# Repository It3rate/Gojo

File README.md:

# Gojo

Gojo is a lean extraction of the current Gojo kernel and tests from the older Core4 workspace.

The central rule is that meaning should live in inspectable Gojo structure: carriers, locations, relations, unit shapes, slots, residue, timelines, and tension. Helper code may build or read that structure, but it should not become the source of meaning.

For reusable encoding code, start with the [shared encoding core](Gojo.Encoding/Core/README.md):
packed storage and ports, native laws and machines, and connected construction
reads promoted from the experiments. New studies can reuse these mechanisms
while keeping unfinished additions local.

For the research, start with the [experiment overview](experiments/OVERVIEW.md):
a chronological guide to the studies in `experiments/`, with each study's
question, results, conclusions and links to the evidence.

The [evidence calculation fixture](Gojo/docs/GojoEvidenceCalculationFixture.md)
tests finite Bayesian conditioning, question orientation, evidence dependence
and empirical support using native unmeasured partitions. Its
[gallery](experiments/QualitativeFrieze/results/evidence-calculation/gallery.html)
uses square continuations to check calculation laws, with supplied likelihoods.

The [weighted shape experiment](Gojo/docs/GojoWeightedShapeEvidence.md) applies
those laws to the 100-shape corpus, comparing the same frozen receiver
proposals under estimated likelihoods and revisable priors. Its
[gallery](experiments/QualitativeFrieze/results/weighted-shapes/gallery.html)
keeps source audits separate from conditional selection weights.

The [mixed curve study](Gojo/docs/GojoQualitativeCurveEvidence.md) adds native
straight, quadratic and cubic constructions, tangent/corner/cusp reads, and
explicit interior and gap-completion premises. Its
[gallery](experiments/QualitativeFrieze/results/curve-evidence/gallery.html)
compares 24 sources and 72 receiver constructions on supplied anonymous endpoint
scaffolds, including a weak whole-shape diamond read alongside local notches.

The [compound ornament study](Gojo/docs/GojoOrnamentCompositionStudy.md) composes
curved bands into shared motifs, mirrored placements, feedback orbits and
two-dimensional fields. Its [16-design gallery](experiments/QualitativeFrieze/results/ornament-composition/gallery.html)
retains frames, repeat correspondence and separately assessed colour intentions.

The [substrate ornament study](Gojo/docs/GojoOrnamentSubstrateStudy.md) keeps
continuous strands independent of their repeat events. Its
[12-design gallery](experiments/QualitativeFrieze/results/ornament-substrate/gallery.html)
includes weave, twill, wave/ogee courses and curved interlocking cells, with
shared local profiles and complete opposite-boundary correspondence.

The [integrated motif pass](Gojo/docs/GojoOrnamentIntegratedStudy.md) adds larger
rooted leaves and landmark florets while preserving those exact mesh paths.
Its [before/after gallery](experiments/QualitativeFrieze/results/ornament-integrated/gallery.html)
exposes native endpoint and straight-interior attachments, tangent reads and
the carried earlier decoration.

The [interior ornament pass](Gojo/docs/GojoOrnamentInteriorStudy.md) develops
multi-part flowers, fans and scrolls within mesh compartments, with native
interior construction landmarks and reusable guide-derived petal profiles.
See the [before/after inspector](experiments/QualitativeFrieze/results/ornament-interior/gallery.html)
and [all new designs](experiments/QualitativeFrieze/results/ornament-interior/designs.html).

The [path and band study](Gojo/docs/GojoPathBandStudy.md) connects source paths,
paired sides, selected occupancy, caps/continuation and local crossing order.
Its [22-case gallery](experiments/QualitativeFrieze/results/path-bands/gallery.html)
shows narrow and broad constructions while retaining the same native paths.

The [curve refinement study](Gojo/docs/GojoCurveRefinementStudy.md) adds relative
fullness, directional and tangent-curvature balance, provisional interiors and
centre/enclosure contexts. Its
[112-case gallery](experiments/QualitativeFrieze/results/curve-refinement/gallery.html)
compares native cue bands, local receiver fitting and revisable completion
defaults while retaining contrary evidence and unresolved interpretations.

The [relational shape study](Gojo/docs/GojoRelationalShapeStudy.md) reconstructs
100 sources with separate pairwise spatial cues, length and angle equivalence,
and qualitative support and opposition. Its
[gallery](experiments/QualitativeFrieze/results/relational-shapes/gallery.html)
compares observation, requested completion, sparse evidence and a control
withholding equivalence. Layout and closure remain revisable hypotheses.

The [joint composition study](Gojo/docs/GojoJointCompositionReconstruction.md)
reconstructs native shapes from anonymous joints, ordinal positions and separate
symmetry evidence. Its [gallery](experiments/QualitativeFrieze/results/joint-reconstruction/gallery.html)
compares three authored policies, retained assumptions and message-only feedback;
this composition round does not train a model.

The [ornament learning pilot](Gojo/docs/GojoOrnamentLearningPilot.md) trains a
portable native route dictionary from a streamed curriculum and tests partial
evidence, conflicts and held-out constructions. Its
[gallery](experiments/QualitativeFrieze/results/ornament-learning/gallery.html)
keeps teacher observations, open correspondence and generated hypotheses
separate; [whole-family holdout](experiments/QualitativeFrieze/results/ornament-learning-family/gallery.html)
exposes the limits of route recall without compositional learning.

The [native interior discovery study](Gojo/docs/GojoNativeInteriorDiscovery.md)
finds local enclosures in lattice passages through native word order and cyclic
ray walks, then reads side structure, notches and zigzags with explicit evidence.
Its [gallery](experiments/QualitativeFrieze/results/native-interiors/gallery.html)
separates observed boundaries from proposed gap closures; the
[overview](experiments/QualitativeFrieze/results/native-interiors/overview.html)
compares twenty source patches.

The [native lattice evidence study](Gojo/docs/GojoNativeLatticeEvidence.md)
connects executed ornament graphs to query-directed geometric evidence through
published ports. Its [gallery](experiments/QualitativeFrieze/results/native-lattice-evidence/gallery.html)
compares actual source supports, requested premises and derived boundary views,
including missing geometry and bounded searches.

The [structural potential study](Gojo/docs/GojoStructuralPotential.md) connects
partial evidence to query-directed relational completions. Its
[gallery](experiments/QualitativeFrieze/results/structural-potential/gallery.html)
keeps supporting-line possibilities, finite support, and introduced assumptions
separate from the original source.

The [reusable rule-pack study](Gojo/docs/GojoReusableRulePacks.md) applies the same
native contracts to ornaments, glyphs and path networks, then connects defaults
to provisional generation and revision. Its
[interactive gallery](experiments/QualitativeFrieze/results/rule-pack-transfer/gallery.html)
keeps source evidence, construction assumptions and actual output checks separate.

The [ornament default study](Gojo/docs/GojoOrnamentDefaults.md) separates required
structure, revisable defaults and deliberately unused cues across 72 native
drawings. Its [interactive gallery](experiments/QualitativeFrieze/results/ornament-defaults/gallery.html)
shows which alternatives survive changes to count, symmetry, overlap and
proportion expectations, with counterexamples and missing evidence retained.

The [ornament concept-equivalence study](Gojo/docs/GojoOrnamentConceptEquivalence.md)
compares 38 native designs under explicit whole-arrangement questions. Its
[interactive gallery](experiments/QualitativeFrieze/results/ornament-concepts/gallery.html)
shows how a rosette, fan and branching window can share one route concept while
remaining visually different, and exposes designs that agree with earlier local
questions but violate the requested whole arrangement.

## Quick Start

Work directly on `master` and commit completed, verified checkpoints locally.
Create a feature branch only when requested. Pushing remains a separate action.

```powershell
dotnet test Gojo.slnx
```

## Layout

The [Minds notebook](experiments/Minds/README.md) retains the two-space feedback and
prospective prediction experiments, including protocols, recorded outcomes,
independent comparisons and the static `/minds/` viewers.

```text
Gojo/                       numeric and structural kernel
  Core/                     carriers, locations, relations, tick refs, unit shapes
  Structures/               repeat surfaces, claims and other structural helpers
  Patterns/                 placeholders, bindings and repeat controllers
  Equations/                relation-shaped equations and reads
  ConceptSurface/           low-resolution concept-surface experiments
  axioms/                   current model notes
  docs/                     model documentation and experiment reports
Gojo.Encoding/              experimental encoding and concept-address layer
Gojo.EncodingC/             lean bit-level encoding of computing structures (exploratory)
Applications/
  GojoCAD/                  graphical and geometric Gojo structure
  GojoDraw/                 Skia presentation adapter over GojoCAD
Visualizations/
  Gojo.Blocks/               interactive structural explorer
  Gojo.Blocks.Browser/       browser host for Blocks
  Gojo.GearShapeLadder/      gear and shape-ladder explorer
  Gojo.GearShapeLadder.Browser/
  GojoCAD.SketchViewer/      sketch inspection UI
  GojoCAD.SketchViewer.Browser/
  GojoDraw.Visualizer/       demo app exercising GojoDraw
  Gojo.Demos.Web/            static experiment viewers
Tests/                      every test project, retaining its existing name
experiments/                research fixtures, runners and retained results
  Minds/                    two-space feedback and prediction notebook
artifacts/                  generated build and export artifacts
```

Solution folders follow these same categories. Each solution keeps its existing
project selection; some retained experiments and viewers are run directly.
Project names, assemblies and namespaces remain unchanged by this layout.

## Extracted From

This repo was extracted from the Core4 workspace so Gojo can be read and developed without the older Core4, runtime, demo, SIMD, and probe projects in the way.

Older ideas worth remembering are summarized in the
[Core4 idea inventory](Gojo/docs/LegacyCore4IdeaInventory.md); they should be
re-expressed Gojo-natively before becoming code.

## Simulation and learning experiments

The experiments are retained on `master`, including the Minds notebook,
Phototaxis swimming demo, prediction and market studies, and later learning,
composition and lifecycle work. Read the [chronological overview](experiments/OVERVIEW.md)
for findings, or the [experiment index](experiments/README.md) for runnable
commands, retained results and the lossless large-result restore helper.

The [qualitative recognition study](Gojo/docs/GojoQualitativeRecognition.md)
examines recurring motifs and larger flow arrangements from segment observations
with construction history and position words withheld. Its retained
[interactive gallery](experiments/QualitativeFrieze/results/qualitative-recognition/gallery.html)
compares several interpretations of each field.
The [evidence and placement follow-up](Gojo/docs/GojoQualitativeRecognitionFirmness.md)
separates admission from demonstrated flow, adds ordinal chamber placement,
and rechecks preserved motifs against local changes in its
[gallery](experiments/QualitativeFrieze/results/recognition-firmness/gallery.html).
The [hierarchical recognition study](Gojo/docs/GojoHierarchicalRecognition.md)
composes motifs, chamber roles and row programs across opaque interfaces.
Its [interactive gallery](experiments/QualitativeFrieze/results/hierarchical-recognition/gallery.html)
follows questions downward and actual evidence back upward, including contrary,
ambiguous and capacity-limited answers.
The [ornament program encoding](Gojo/docs/GojoOrnamentProgramEncoding.md)
separates shared motifs and periodic layout rules from parameter bindings,
sampling windows and expanded execution. Its
[gallery](experiments/QualitativeFrieze/results/ornament-program/gallery.html)
includes six samples from a saved native program, with standalone replay.
The [Bourgoin construction study](Gojo/docs/GojoBourgoinEncodingStudy.md)
tests a broader source-derived vocabulary and explicit seams between repeated
units. Its [comparison gallery](experiments/QualitativeFrieze/results/bourgoin-patterns/gallery.html)
places native generated fields beside the cited historical diagrams.
The [source-correction follow-up](Gojo/docs/GojoBourgoinRefinementStudy.md)
uses local lattice refinements and closed negative chambers to improve those
reconstructions, with preserved first-pass images and source overlays.
The [construction vocabulary study](Gojo/docs/GojoBourgoinVocabularyStudy.md)
adds twenty source-based skeletons, finite curved profiles and a
[single-sheet atlas](experiments/QualitativeFrieze/results/bourgoin-patterns/overview.html),
while separating authored explanations from computed graph reads.
The [contact and course study](Gojo/docs/GojoBourgoinContactAndCourseStudy.md)
refines partial-side sliding contacts, flat-tipped stars, slender arms and
open ribbon courses while retaining the earlier constructions for comparison.
The [lattice construction ladders](Gojo/docs/GojoLatticeConstructionLadders.md)
retain actual grid ancestors through 19 related constructions, with separate
current-graph questions and an explicit history-forgetting experiment. Their
[interactive gallery](experiments/QualitativeFrieze/results/lattice-ladders/gallery.html)
lets you walk each branch and compare its earlier bases.
The [hundred-lattice catalogue](Gojo/docs/GojoLatticeCatalogue.md) expands this
into twenty parameterized families with explicit constraint withdrawal,
reformulation, coarse compartments and finite rule assessments. Its
[gallery](experiments/QualitativeFrieze/results/lattice-catalogue/gallery.html)
shows construction strips and supports local ratings; the
[whole sheet](experiments/QualitativeFrieze/results/lattice-catalogue/overview.html)
compares all hundred unfilled scaffolds.
The [geometric transformation follow-up](Gojo/docs/GojoLatticeGeometryTransformations.md)
then changes the actual spans with notches, bends, cuts, shared runs and moved
hubs. Its [before/after gallery](experiments/QualitativeFrieze/results/lattice-transformations/gallery.html)
separates real support change from regrouping or rescaling the same pattern.
The [interior-first study](Gojo/docs/GojoLatticeInteriorStudy.md) merges actual
atomic faces into non-overlapping cells, with explicit competing seam claims.
Its [hundred-case gallery](experiments/QualitativeFrieze/results/lattice-interiors/gallery.html)
compares filled interiors, outlines and removed dividers.
The [Gestalt exploration plan](Gojo/docs/GojoGestaltViewsExploration.md) proposes
overlapping cue-based reads and compares constructive contexts for the same shape.
The [construction-context experiments](Gojo/docs/GojoConstructionContextExperiments.md)
exercise equal support with different edit scopes, constraint withdrawal,
optional construction memory and overlapping views consumed by new flow.
Their [interactive gallery](experiments/QualitativeFrieze/results/construction-contexts/gallery.html)
and [all-step overview](experiments/QualitativeFrieze/results/construction-contexts/overview.html)
compare seventeen path steps and three shared-field constructions.
The [junction interpretation study](Gojo/docs/GojoJunctionInterpretationExperiments.md)
then separates actual joins from projected crossings, endpoint contacts and
speculative gap continuations. Its [gallery](experiments/QualitativeFrieze/results/junction-interpretations/gallery.html)
retains competing cut and depth readings without altering source topology.
The [coloured ornament collection](experiments/QualitativeFrieze/results/coloured-ornament/gallery.html)
adds native landmark-bound petals, leaves and medallions, with three selectable
focuses guided by Jones's colour and hierarchy proposals. Its
[study](Gojo/docs/GojoColouredOrnamentStudy.md) also corrects B32's diagonal continuation.
The [full ornament design collection](experiments/QualitativeFrieze/results/ornament-designs/gallery.html)
extends all 36 skeletons into 108 separately constructed designs, with
geometric fields, intermediate flowers and foliage, and fine local details.
Its [single-page sheet](experiments/QualitativeFrieze/results/ornament-designs/overview.html)
puts all three versions of every skeleton together; the
[construction study](Gojo/docs/GojoOrnamentDesignCollection.md) describes the
finer unmeasured vocabulary and native attachment evidence.
The [detail study](experiments/QualitativeFrieze/results/ornament-details/gallery.html)
develops ten richer motifs and four scaffold-following B02/B05 integrations,
with one-unit close-ups and a single comparison sheet.
The [refined 108-design collection](experiments/QualitativeFrieze/results/ornament-refined/gallery.html)
extends that vocabulary across the catalogue with optional curves over native
guides, angular comparisons and close-ups. The
[curve studies](experiments/QualitativeFrieze/results/ornament-curves/gallery.html)
isolate the vine, corrected curl and interrupted guilloche.
The [B08–B14 interior studies](experiments/QualitativeFrieze/results/ornament-refined/interiors-gallery.html)
develop larger flowers, interior gardens and four-colour interlocking shapes,
with [24 designs on one sheet](experiments/QualitativeFrieze/results/ornament-refined/interiors.html).
The [silhouette and colour review](experiments/QualitativeFrieze/results/ornament-refined/balance.html)
compares the enlarged detail with its previous checkpoint; a
[conceptual-complexity table](experiments/QualitativeFrieze/results/ornament-refined/complexity.html)
keeps reviewed reusable vocabularies separate from native encoding counts.
The [public ornament gallery](https://gojo.inklingai.ca/ornaments/flowing-grammar/)
includes all 108 designs and their executed-unit views. Its bounded website
edition keeps the research archives and alternate construction views in this checkout.

For example, run the prospective-prediction experiment and its notebook tests
from the repository root:

```powershell
dotnet run --project experiments/Minds -- --experiment3
dotnet test Tests/Minds.Tests/Minds.Tests.csproj
```

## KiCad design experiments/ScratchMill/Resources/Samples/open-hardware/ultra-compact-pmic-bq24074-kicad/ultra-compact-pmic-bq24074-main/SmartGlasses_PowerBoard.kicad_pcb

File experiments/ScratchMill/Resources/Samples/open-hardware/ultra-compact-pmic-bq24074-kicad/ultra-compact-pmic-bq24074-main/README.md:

# ultra-compact-pmic-bq24074

## 1. Project Overview
This repository contains the design files for an ultra-compact (11mm x 30mm) Power Management Unit (PMU) specifically engineered for wearable AR/VR devices. The module is built around the **Texas Instruments BQ24074** PMIC, providing a unified solution for USB Type-C power input, Lithium-Polymer battery charging, and regulated system output (VOUT).

The design prioritizes high power density, stringent thermal management, and IPC-compliant routing within a highly constrained physical footprint.

## 2. Technical Specifications
* **Form Factor:** 11mm x 30mm (Edge-mount optimized)
* **PMIC:** TI BQ24074 (Standalone Li-Ion/Li-Pol Charger with Power Path Management)
* **Input (VBUS):** USB Type-C Receptacle (6-Pin, Power Only, Edge-Mount)
* **Output Interface:** 5-Pin 0.5mm Pitch Horizontal FPC Connector
* **Protection:** ESD and Transient Voltage Suppression (TVS) on VBUS (DFN1006 package)
* **Component Sizing:** Optimized for 0201 (Imperial) passive components to minimize parasitic inductance and footprint.

## 3. Engineering Analysis & Design Methodology

### 3.1 Layout and I/O Integration
* **Mechanical Alignment:** The J1 Type-C connector is positioned with mechanical GND pads flush to the board edge (Edge.Cuts), ensuring structural integrity and precise alignment for wearable frames.
* **Isolation Zones:** Battery termination pads (BATT+/BATT-) are isolated from the main PMIC logic to prevent short circuits during manual soldering/assembly.

### 3.2 Power Integrity and Thermal Strategy
* **High-Current Pathing:** VBUS, VOUT, and BAT tracks are routed with a minimum width of 0.5mm to sustain peak charging currents and minimize IR drop.
* **Decoupling Protocol:** Low-ESR ceramic capacitors (C1, C2) are placed in immediate proximity to the PMIC pins to suppress high-frequency noise and ensure voltage stability.
* **Ground Plane & Via Stitching:** A dual-layer solid ground plane strategy was employed. Isolated GND islands on the top layer are interconnected to the primary bottom layer ground plane through a high-density via stitching matrix. This facilitates both low-impedance return paths and efficient thermal dissipation for the BQ24074.

### 3.3 Verification
* **DRC Compliance:** 0 Design Rule Check (DRC) violations based on 0.1mm minimum clearance constraints.
* **Manufacturing Ready:** All footprints and clearances are verified for standard SMT assembly processes.

## 4. Repository Structure

The production files are organized according to industry-standard fabrication requirements:

1. **`1_Gerber_Files/`** : Fabrication data (.gbr) and drill files (.drl) for PCB manufacturing.
2. **`2_Pick_And_Place/`** : Component centroid data (.pos / .csv) for automated SMT assembly.
3. **`3_BOM_List/`** : Consolidated Bill of Materials including manufacturer part numbers and footprints.
4. **`4_Documentation/`** : High-resolution schematic (PDF) and design specifications.

## 5. Mechanical Integration Note
The current revision (Rev 1.0) focuses on electrical validation and thermal optimization. 3D STEP models for mechanical components (USB-C, FPC, and Tactile Switch) are excluded from this release to allow for custom mechanical alignment with specific frame geometries.

## 6. License
This project is licensed under the **CERN Open Hardware Licence Version 2 - Permissive (CERN-OHL-P)**. See the `LICENSE` file for more details.
---
*Designer:* **Mustafa Ege KILIÇ** *Date:*  08 April 2026  
*Project Version:* Rev 1.0

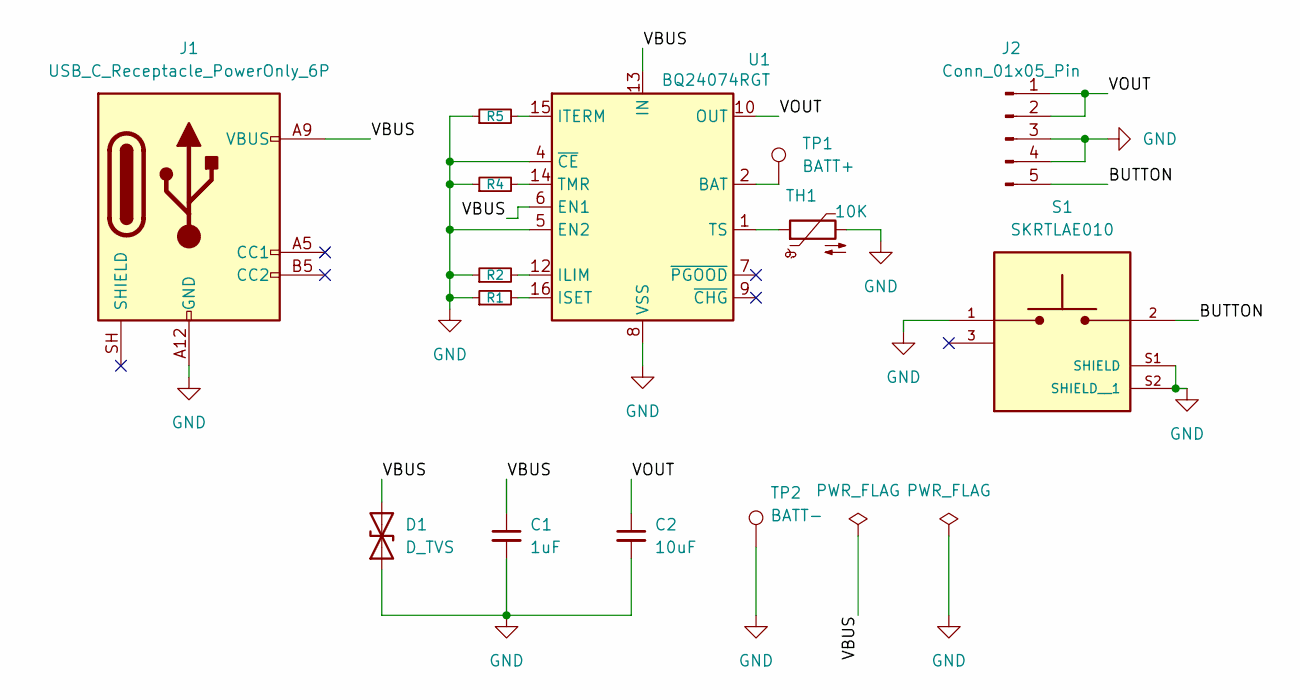
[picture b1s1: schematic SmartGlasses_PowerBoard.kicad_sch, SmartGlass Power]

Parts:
C1: 1uF; C_0402_1005Metric
C2: 10uF; C_0603_1608Metric
D1: D_TVS; D_0402_1005Metric
J1: USB_C_Receptacle_PowerOnly_6P; CONN_USB4135-GF-A_GCT
J2: Conn_01x05_Pin; CON_522710579_MOL
R1: 1.8K; R_0201_0603Metric
R2: 10K; R_0201_0603Metric
R4: 46.4; R_0201_0603Metric
R5: 1.1K; R_0201_0603Metric
S1: SKRTLAE010; SW_SKRTLAE010; PARTREV --
TH1: 10K; R_0603_1608Metric
TP1: BATT+; TestPoint_Pad_3.0x3.0mm
TP2: BATT-; TestPoint_Pad_3.0x3.0mm
U1: BQ24074RGT; VQFN-16-1EP_3x3mm_P0.5mm_EP1.6x1.6mm

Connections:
/BUTTON: J2.5, S1.2
/VBUS: C1.1, D1.2 (A2), J1.A9 (VBUS), J1.B9 (VBUS), U1.6 (EN1), U1.13 (IN)
/VOUT: C2.1, J2.1, J2.2, U1.10 (OUT), U1.11 (OUT)
GND: C1.2, C2.2, D1.1 (A1), J1.A12 (GND), J1.B12 (GND), J2.3, J2.4, R1.1, R2.1, R4.1, R5.1, S1.1, S1.S1 (SHIELD), S1.S2 (SHIELD__1), TH1.2, TP2.1 (1_1), U1.4 (~CE), U1.5 (EN2), U1.8 (VSS), U1.17 (VSS)
unnamed: TP1.1 (1_1), U1.2 (BAT), U1.3 (BAT)
unnamed: R2.2, U1.12 (ILIM)
unnamed: R1.2, U1.16 (ISET)
unnamed: R5.2, U1.15 (ITERM)
unnamed: R4.2, U1.14 (TMR)
unnamed: TH1.1, U1.1 (TS)

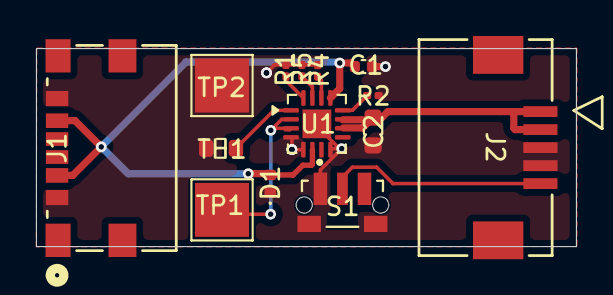
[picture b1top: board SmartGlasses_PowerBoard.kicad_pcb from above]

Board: 2 copper layers, 30.0 x 11.0 mm, 14 parts (0 on the bottom side), 10 nets.

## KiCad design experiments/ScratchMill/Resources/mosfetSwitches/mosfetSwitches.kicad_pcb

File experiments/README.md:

# Experiments and retained research

**Start with the [chronological experiment overview](OVERVIEW.md).** It covers
both this folder and `experiments/Minds/`, explaining what each study tried, what happened
and what can be concluded, with links to the detailed evidence.

This folder contains interpretation, prediction, market, swimming,
primitive-number, local-learning, composition and service-economy studies.
Their limitations and failed trials remain part of the record. The table below
provides direct access to the swimming and subsequent learning suite; the
overview includes the earlier studies and Minds as well.

See [Primitive numbers and control](PRIMITIVE-NUMBER-ANALYSIS.md) for the conceptual
mapping from presence, orientation and coarse regions to calibrated quantities,
prediction and control, grounded in these experiments.

| Study | Source and documentation | Retained results / review |
| --- | --- | --- |
| Motifs integrated with retained meshes | [Model, design review and limits](../Gojo/docs/GojoOrnamentIntegratedStudy.md), [native attachment ports](QualitativeFrieze/Composition/OrnamentMotifAttachment.cs), [rooted corpus](QualitativeFrieze/Composition/OrnamentIntegratedCorpus.cs) | [12 before/after designs](QualitativeFrieze/results/ornament-integrated/gallery.html), [whole sheet](QualitativeFrieze/results/ornament-integrated/overview.html) |
| Continuous strands and curved periodic cells | [Model, historical sources and limits](../Gojo/docs/GojoOrnamentSubstrateStudy.md), [native substrate](QualitativeFrieze/Composition/OrnamentSubstrate.cs), [reusable profile corpus](QualitativeFrieze/Composition/OrnamentSubstrateCorpus.cs) | [12 designs / four views](QualitativeFrieze/results/ornament-substrate/gallery.html), [whole sheet](QualitativeFrieze/results/ornament-substrate/overview.html) |
| Compound ornaments, repetition and colour intentions | [Model, repertoire and gaps](../Gojo/docs/GojoOrnamentCompositionStudy.md), [native composition](QualitativeFrieze/Composition/OrnamentBandComposition.cs), [colour intentions](QualitativeFrieze/Composition/OrnamentColourIntent.cs) | [16 designs / two readings each](QualitativeFrieze/results/ornament-composition/gallery.html), [whole sheet](QualitativeFrieze/results/ornament-composition/overview.html) |
| Paths, paired boundaries and occupied bands | [Model and findings](../Gojo/docs/GojoPathBandStudy.md), [native ruled-band surface](QualitativeExecution/QualitativeBand.cs), [repertoire and width rungs](QualitativeFrieze/Composition/BandEvidenceCorpus.cs) | [22 cases / 88 views](QualitativeFrieze/results/path-bands/gallery.html), [whole sheet](QualitativeFrieze/results/path-bands/overview.html) |
| Tangency, fullness and completion defaults | [Model, research and findings](../Gojo/docs/GojoCurveRefinementStudy.md), [native quality reads](QualitativeExecution/CurveShapeQualities.cs), [detached cue bands](QualitativeFrieze/Composition/CurveRefinementMessage.cs), [coarse context](QualitativeFrieze/Composition/CurveContextRead.cs) | [112-case comparison](QualitativeFrieze/results/curve-refinement/gallery.html), [whole sheet](QualitativeFrieze/results/curve-refinement/overview.html) |
| Mixed curve evidence and sparse completion | [Encoding and results](../Gojo/docs/GojoQualitativeCurveEvidence.md), [native curve surface](QualitativeExecution/QualitativeCurve.cs), [public scaffold and completion](QualitativeFrieze/Composition/CurveEvidenceScene.cs) | [24 cases and 72 candidates](QualitativeFrieze/results/curve-evidence/gallery.html), [whole sheet](QualitativeFrieze/results/curve-evidence/overview.html) |
| Weighted evidence over 100 shapes | [Model and training protocol](../Gojo/docs/GojoWeightedShapeEvidence.md), [generic compatibility channel](QualitativeExecution/CompatibilityEvidence.cs), [native weighting](QualitativeFrieze/Composition/ShapeEvidenceWeighting.cs) | [Same-pool comparison](QualitativeFrieze/results/weighted-shapes/gallery.html), [whole sheet](QualitativeFrieze/results/weighted-shapes/overview.html) |
| Evidence calculation before measured geometry | [Laws and limits](../Gojo/docs/GojoEvidenceCalculationFixture.md), [finite model conditioning](QualitativeExecution/StatisticalEvidence.cs), [empirical support](QualitativeExecution/EvidenceSupport.cs) | [Inspect calculations](QualitativeFrieze/results/evidence-calculation/gallery.html), [whole sheet](QualitativeFrieze/results/evidence-calculation/overview.html) |
| Relational shape composition and revisable evidence | [Design and limits](../Gojo/docs/GojoRelationalShapeStudy.md), [independent corpus](QualitativeFrieze/Composition/RelationalShapeCorpus.cs), [equivalence stream](QualitativeFrieze/Composition/JointEquivalenceEvidence.cs), [qualitative evidence contexts](QualitativeFrieze/Composition/StructuralEvidenceStreams.cs) | [Four contexts per source](QualitativeFrieze/results/relational-shapes/gallery.html), [source sheet](QualitativeFrieze/results/relational-shapes/overview.html) |
| Anonymous joint-stream composition | [Design and limits](../Gojo/docs/GojoJointCompositionReconstruction.md), [independent message](QualitativeFrieze/Composition/JointShapeDescription.cs), [native reconstruction](QualitativeFrieze/Composition/JointShapeReconstruction.cs) | [Three attempts per source](QualitativeFrieze/results/joint-reconstruction/gallery.html), [source sheet](QualitativeFrieze/results/joint-reconstruction/overview.html) |
| Persistent native ornament learning | [Protocol and limits](../Gojo/docs/GojoOrnamentLearningPilot.md), [streamed corpus](QualitativeFrieze/Learning/OrnamentLearningCorpus.cs), [native learned memory](QualitativeFrieze/Learning/OrnamentLearningMemory.cs) | [Partial-evidence gallery](QualitativeFrieze/results/ornament-learning/gallery.html), [whole-family holdout](QualitativeFrieze/results/ornament-learning-family/gallery.html) |
| Native interior discovery and conditional closure | [Methods and limits](../Gojo/docs/GojoNativeInteriorDiscovery.md), [native boundary discovery](QualitativeFrieze/NativeInteriorTopology.cs), [feature reads](QualitativeFrieze/NativeInteriorFeatures.cs) | [Twenty lattice sources](QualitativeFrieze/results/native-interiors/gallery.html), [whole sheet](QualitativeFrieze/results/native-interiors/overview.html) |
| Native lattice sources and derived query evidence | [Methods and limits](../Gojo/docs/GojoNativeLatticeEvidence.md), [calculated supplier](QualitativeFrieze/NativeLineSupplier.cs), [publication boundary](QualitativeFrieze/NativeLinePublication.cs) | [Thirteen sources and selected boundaries](QualitativeFrieze/results/native-lattice-evidence/gallery.html), [whole sheet](QualitativeFrieze/results/native-lattice-evidence/overview.html) |
| Structural potential and query-directed completion | [Methods and limits](../Gojo/docs/GojoStructuralPotential.md), [native evidence reader](QualitativeFrieze/StructuralEvidenceRules.cs), [candidate construction](QualitativeFrieze/StructuralPotential.cs) | [Twelve inspectable cases](QualitativeFrieze/results/structural-potential/gallery.html), [whole sheet](QualitativeFrieze/results/structural-potential/overview.html) |
| Reusable rule packs and revisable generation | [Methods and findings](../Gojo/docs/GojoReusableRulePacks.md), [portable pack](QualitativeFrieze/StructuralRulePack.cs), [generation engine](QualitativeFrieze/RevisableRuleGeneration.cs) | [Transfer and revision gallery](QualitativeFrieze/results/rule-pack-transfer/gallery.html), [whole sheet](QualitativeFrieze/results/rule-pack-transfer/overview.html) |
| Ornament requirements, defaults and deliberate omissions | [Methods and findings](../Gojo/docs/GojoOrnamentDefaults.md), [native policy reader](QualitativeFrieze/OrnamentDefaultsPolicy.cs) | [72 constructions and rule interventions](QualitativeFrieze/results/ornament-defaults/gallery.html), [whole sheet](QualitativeFrieze/results/ornament-defaults/overview.html) |
| Phototaxis swimmers, compact backend and cognitive trials | [Simulation](Phototaxis/README.md), [browser launcher](Phototaxis.Browser/Start-Preview.ps1), [headless runner](Phototaxis.Runner/Program.cs) | [Earlier runs](../artifacts/phototaxis) |
| Sampling into primitive distinctions | [Sampling emergence](SamplingEmergence/README.md) | [Review](../artifacts/sampling-emergence) |
| Relative signals and decaying reference | [Relative signals](RelativeSignals/README.md) | [Runs](../artifacts/relative-signals) |
| Primitive agency and lookup arithmetic | [Primitive agency](PrimitiveAgency/README.md) | [Runs](../artifacts/primitive-agency), [sweep](../artifacts/primitive-agency-sweep) |
| Primitive foraging | [Primitive forager](PrimitiveForager/README.md) | [Review](../artifacts/primitive-forager) |
| Four local/composite learning experiments | [Primitive learning](PrimitiveLearning/REPORT.md) | [Runs](../artifacts/primitive-learning) |
| Composite emergence | [Composite emergence](CompositeEmergence/REPORT.md) | [Runs](CompositeEmergence/results) |
| Retry, retention and lifecycle adaptation | [Adaptive lifecycle](AdaptiveLifecycle/REPORT.md) | [Runs](AdaptiveLifecycle/results) |
| Local service economy | [Ecology report](UtilityEcology/REPORT.md) | [Review](UtilityEcology/review.html) |
| Progress alongside error | [Progress report](UtilityEcology/PROGRESS-REPORT.md) | [Review](UtilityEcology/progress-review.html) |
| Finite seed and paid candidate admission | [Seed report](UtilityEcology/SEED-REPORT.md) | [Review](UtilityEcology/seed-review.html) |
| Qualitative motif and disposition recognition | [Recognition report](../Gojo/docs/GojoQualitativeRecognition.md), [observation adapter](QualitativeFrieze/QualitativeRecognitionObservation.cs) | [Interactive gallery](QualitativeFrieze/results/qualitative-recognition/gallery.html) |
| Recognition evidence and ordinal placement | [Firmness report](../Gojo/docs/GojoQualitativeRecognitionFirmness.md), [evidence reader](QualitativeFrieze/QualitativeDispositionEvidence.cs), [placement](QualitativeFrieze/QualitativeRecognitionPlacement.cs) | [Interactive gallery](QualitativeFrieze/results/recognition-firmness/gallery.html) |
| Hierarchical pattern recognition | [Report](../Gojo/docs/GojoHierarchicalRecognition.md), [phase grammar](QualitativeFrieze/QualitativePatternGrammar.cs), [layered study](QualitativeFrieze/QualitativeHierarchicalRecognitionStudy.cs) | [Interactive gallery](QualitativeFrieze/results/hierarchical-recognition/gallery.html) |
| Executable ornament program encoding | [Format and findings](../Gojo/docs/GojoOrnamentProgramEncoding.md), [native program](QualitativeFrieze/OrnamentProgram.cs) | [Six samples and runnable archive](QualitativeFrieze/results/ornament-program/gallery.html) |
| Bourgoin geometric ornament constructions | [Findings and sources](../Gojo/docs/GojoBourgoinEncodingStudy.md), [native field assembler](QualitativeFrieze/OrnamentProgramField.cs) | [Source comparison gallery and replayable packets](QualitativeFrieze/results/bourgoin-patterns/gallery.html) |
| Bourgoin source corrections and compartment refinements | [Corrections and checks](../Gojo/docs/GojoBourgoinRefinementStudy.md), [refined diamond fields](QualitativeFrieze/BourgoinPatternLibrary.DiamondFields.cs), [interlocking chambers](QualitativeFrieze/BourgoinPatternLibrary.InterlockingShapes.cs) | [Fifteen cases, first-pass comparisons and overlays](QualitativeFrieze/results/bourgoin-patterns/gallery.html) |
| Bourgoin construction vocabulary | [Shared identities, layers and finite curved profiles](../Gojo/docs/GojoBourgoinVocabularyStudy.md), [exact native construction read](QualitativeFrieze/BourgoinConstructionRead.cs) | [Thirty-six constructions on one sheet](QualitativeFrieze/results/bourgoin-patterns/overview.html) |
| Native lattice construction ladders | [Retained bases, current-shape reads and deliberate forgetting](../Gojo/docs/GojoLatticeConstructionLadders.md), [native ladder](QualitativeFrieze/QualitativeLatticeLadder.cs) | [Nineteen constructions with rung controls](QualitativeFrieze/results/lattice-ladders/gallery.html), [single sheet](QualitativeFrieze/results/lattice-ladders/overview.html) |
| One hundred editable lattice constructions | [Withdrawal, reformulation, rules and review](../Gojo/docs/GojoLatticeCatalogue.md), [twenty native recipe families](QualitativeFrieze/LatticeCatalogueRecipes.Families.cs) | [Catalogue and ratings](QualitativeFrieze/results/lattice-catalogue/gallery.html), [whole sheet](QualitativeFrieze/results/lattice-catalogue/overview.html), [construction strips](QualitativeFrieze/results/lattice-catalogue/construction-strips.html) |
| Actual geometric lattice transformations | [Notches, shared runs, cuts, hubs and contact agreements](../Gojo/docs/GojoLatticeGeometryTransformations.md), [native surgery](QualitativeFrieze/LatticeGeometrySurgery.cs) | [Before/after gallery](QualitativeFrieze/results/lattice-transformations/gallery.html), [whole sheet](QualitativeFrieze/results/lattice-transformations/overview.html) |
| Interior-first lattice partitions | [Exclusive cells, shape scale and negotiated seams](../Gojo/docs/GojoLatticeInteriorStudy.md), [native occupancy reader](QualitativeFrieze/InteriorCellPartition.cs) | [Inspect and rate](QualitativeFrieze/results/lattice-interiors/gallery.html), [whole sheet](QualitativeFrieze/results/lattice-interiors/overview.html), [rules and counterexamples](QualitativeFrieze/results/lattice-interiors/rules.html) |
| A grammar in colour | [Native enrichment, finer unmeasured authoring and design hierarchy](../Gojo/docs/GojoOrnamentDesignCollection.md) | [108 designs](QualitativeFrieze/results/ornament-designs/gallery.html), [all designs on one page](QualitativeFrieze/results/ornament-designs/overview.html) |
| Detail that follows the structure | [Parent, direction, cadence and native finite detail](../Gojo/docs/GojoOrnamentDetailStudy.md) | [Ten studies and four integrations](QualitativeFrieze/results/ornament-details/gallery.html), [single sheet](QualitativeFrieze/results/ornament-details/overview.html) |
| A flowing grammar | [Native refinement and selected curve interpretation](../Gojo/docs/GojoOrnamentRefinedCollection.md) | [108 refined designs](QualitativeFrieze/results/ornament-refined/gallery.html), [curve studies](QualitativeFrieze/results/ornament-curves/gallery.html), [single sheet](QualitativeFrieze/results/ornament-refined/overview.html) |

## Fresh checkout

```powershell
git clone -c core.longpaths=true --branch master https://github.com/It3rate/Gojo.git Gojo
cd Gojo
python experiments/ResearchArchive/Restore-LargeResults.py --restore
dotnet test Gojo.slnx -c Release
```

Use Python 3.10 or later and .NET 10. The clone command enables Windows long-path
support for the existing nested sample resources. The browser additionally needs the .NET
WebAssembly workload for its browser project. The archive command restores one
170 MiB forager result from a roughly 3 MiB lossless gzip. It checks both hashes,
keeps identical existing files and refuses conflicting files. All other retained
research records are ordinary Git files. Build outputs and caches are excluded.

Read [archive details](ResearchArchive/README.md) and the
[preservation manifest](ResearchArchive/preservation.json) for the earlier
ignored evidence, including historical test receipts. Source line-ending rules
preserve the current study's captured source hashes on checkout. Old studies
retain their own declared source/provenance and replay limits; publishing them
does not expand those claims.

## Run the latest study or swimming demo

```powershell
dotnet run --project experiments/QualitativeFrieze -c Release -- --joint-reconstruction

dotnet run --project experiments/QualitativeFrieze -c Release -- --ornament-learning --count 4096
dotnet run --project experiments/QualitativeFrieze -c Release -- --recognition-firmness
dotnet run --project experiments/QualitativeFrieze -c Release -- --hierarchical-recognition
dotnet run --project experiments/QualitativeFrieze -c Release -- --ornament-program

dotnet run --project experiments/QualitativeFrieze -c Release -- --bourgoin-patterns

dotnet run --project experiments/QualitativeFrieze -c Release -- --lattice-ladders

dotnet run --project experiments/QualitativeFrieze -c Release -- --lattice-catalogue

dotnet run --project experiments/QualitativeFrieze -c Release -- --lattice-transformations

dotnet run --project experiments/QualitativeFrieze -c Release -- --lattice-interiors
dotnet run --project experiments/UtilityEcology -c Release -- --seed-trial --pilot --phase-length 512 --output experiments/UtilityEcology/results/new-seed-pilot
./experiments/Phototaxis.Browser/Start-Preview.ps1
```

Use a new output directory for future trials. The seed mode is optional; omitting
`--seed-trial` retains the existing ecology modes. Its checked rollback package
remains in `UtilityEcology/backout/seed-trial-20261012/`.

HTML reviews are saved outputs; GitHub's file view shows their source. Read the
Markdown report on GitHub, or serve/open the review locally as its README directs.
No API key is needed for the seed/ecology studies. Optional TypeSafe/Jev trials
read credentials from the environment; credentials are not part of this archive.

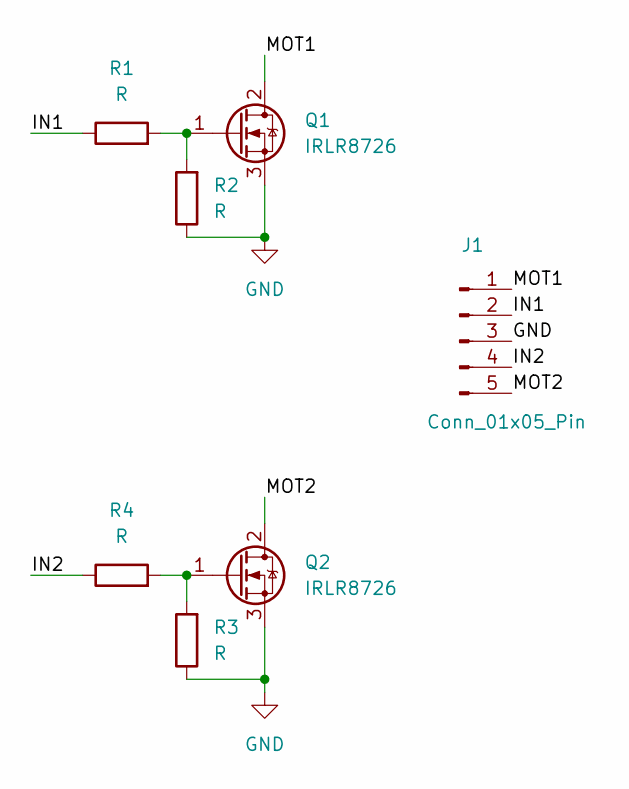
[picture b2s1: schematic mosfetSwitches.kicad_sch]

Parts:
J1: Conn_01x05_Pin; PinHeader_1x05_P2.54mm_Vertical
Q1, Q2: IRLR8726; TO-252-2
R1, R2, R3, R4: R; R_1206_3216Metric_Pad1.30x1.75mm_HandSolder

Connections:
/IN1: J1.2, R1.1
/IN2: J1.4, R4.1
/MOT1: J1.1, Q1.2 (D)
/MOT2: J1.5, Q2.2 (D)
GND: J1.3, Q1.3 (S), Q2.3 (S), R2.1, R3.1
unnamed: Q1.1 (G), R1.2, R2.2
unnamed: Q2.1 (G), R3.2, R4.2

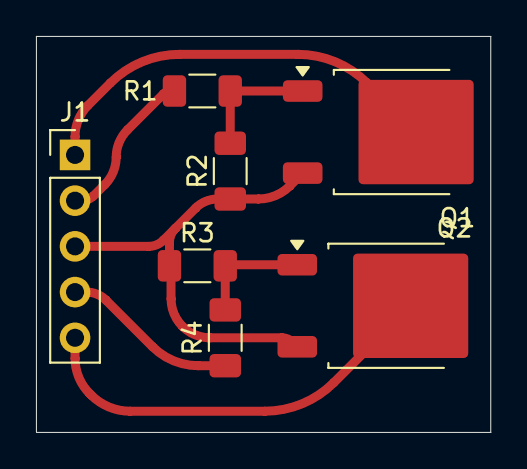
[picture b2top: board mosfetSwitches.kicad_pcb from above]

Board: 2 copper layers, 25.2 x 22.0 mm, 7 parts (0 on the bottom side), 7 nets.

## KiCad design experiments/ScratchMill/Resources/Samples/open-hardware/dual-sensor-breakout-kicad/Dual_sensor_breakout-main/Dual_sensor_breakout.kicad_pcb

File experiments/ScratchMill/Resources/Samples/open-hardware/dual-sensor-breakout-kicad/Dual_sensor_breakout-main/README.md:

# BME280 + MPU6050 Dual Sensor Breakout Board — IoT PCB Design

> A compact dual-sensor breakout board combining the BME280 environmental sensor (temperature, humidity, pressure) and MPU6050 IMU (accelerometer + gyroscope) on a single 2-layer PCB. I2C interface, 3.3V regulated, with proper decoupling and logic-level compatibility — Gerber-ready.

---

## Overview

This project is a **dual-sensor breakout board** combining two of the most widely used sensors in IoT and robotics applications onto a single compact PCB. The **BME280** provides environmental data — temperature, humidity, and barometric pressure — while the **MPU6050** provides 6-axis inertial measurement — 3-axis accelerometer and 3-axis gyroscope.

Both sensors share the I2C bus with separate configurable addresses. The board includes onboard 3.3V regulation, I2C pull-up resistors, and full decoupling — so it connects directly to any microcontroller (Arduino, ESP32, STM32) without additional components.

This breakout demonstrates the ability to design compact sensor hardware for IoT products: proper I2C bus design, mixed-signal layout awareness, and careful decoupling on noise-sensitive sensor circuits.

---

## Specifications

| Parameter          | Value                                    |
|--------------------|------------------------------------------|
| Sensor 1           | BME280 — temperature, humidity, pressure |
| Sensor 2           | MPU6050 — 3-axis accel + 3-axis gyro     |
| Interface          | I2C (shared bus, separate addresses)     |
| BME280 I2C Address | 0x76 (SDO → GND) / 0x77 (SDO → VCC)     |
| MPU6050 I2C Address| 0x68 (AD0 → GND) / 0x69 (AD0 → VCC)     |
| Supply Voltage     | 3.3V – 5V (onboard regulation to 3.3V)  |
| Logic Level        | 3.3V                                     |
| Regulator          | AMS1117-3.3                              |
| PCB Layers         | 2                                        |
| Board Status       | Design complete, DRC passed              |
| Tool               | KiCad                                    |

---

## Design Highlights

### Shared I2C Bus with Address Flexibility
Both sensors share the same SDA/SCL lines. Address select pads (SDO for BME280, AD0 for MPU6050) are exposed as solder jumpers, allowing the I2C address of each sensor to be configured — useful when running multiple boards on the same bus.

### Onboard 3.3V Regulation
The AMS1117-3.3 LDO accepts 3.3V–5V input and regulates down to a clean 3.3V for both sensors. Input and output bulk capacitors ensure stability. Allows the board to be powered directly from a 5V Arduino without any external regulation.

### Proper I2C Pull-Up Resistors
4.7kΩ pull-up resistors on SDA and SCL ensure correct I2C bus voltage levels. Values selected for reliable communication up to 400 kHz (Fast Mode) across the expected trace lengths and capacitance.

### Sensor Decoupling
Each sensor has dedicated 100nF ceramic decoupling capacitors placed as close as possible to the VCC and VDDIO pins — minimising supply noise coupling into the sensitive analog and MEMS measurement circuits.

### Compact Layout
Both ICs, regulation circuitry, decoupling, and pull-ups are placed within a compact footprint suitable for embedding in drone flight controllers, weather stations, wearables, and IoT sensor nodes.

---

## Repository Structure

```
project4-dual-sensor-breakout/
├── schematic/
│   └── dual_sensor_breakout.kicad_sch
├── pcb/
│   └── dual_sensor_breakout.kicad_pcb
├── gerbers/
│   ├── dual_sensor_breakout.GTL
│   ├── dual_sensor_breakout.GBL
│   ├── dual_sensor_breakout.GTO
│   ├── dual_sensor_breakout.GTS
│   ├── dual_sensor_breakout.GBS
│   └── dual_sensor_breakout.DRL
├── bom/
│   └── bom.csv
└── README.md
```

---

## Bill of Materials

| Ref    | Component           | Part Number   | Package    |
|--------|---------------------|---------------|------------|
| U1     | Environmental Sensor| BME280        | LGA-8      |
| U2     | IMU Sensor          | MPU6050       | QFN-24     |
| U3     | 3.3V LDO Regulator  | AMS1117-3.3   | SOT-223    |
| C1–C2  | Bulk Capacitors     | 10µF          | 0805       |
| C3–C6  | Decoupling Caps     | 100nF         | 0402       |
| R1–R2  | I2C Pull-ups        | 4.7kΩ         | 0402       |
| JP1    | BME280 Addr Select  | Solder jumper | —          |
| JP2    | MPU6050 Addr Select | Solder jumper | —          |
| J1     | Pin Header          | 6-pin, 2.54mm | Through-hole |

---

## Pin Header Pinout

| Pin | Signal | Description                  |
|-----|--------|------------------------------|
| 1   | VIN    | 3.3V – 5V power input        |
| 2   | GND    | Ground                       |
| 3   | SDA    | I2C data                     |
| 4   | SCL    | I2C clock                    |
| 5   | INT    | MPU6050 interrupt output     |
| 6   | 3V3    | Regulated 3.3V output        |

---

## Skills Demonstrated

- I2C bus design with multi-device address management
- MEMS sensor layout (BME280, MPU6050) and decoupling strategy
- LDO regulator circuit design
- Solder jumper address select implementation
- Compact mixed-signal PCB layout on 2 layers
- KiCad DRC and Gerber export

---

## Use Cases

- IoT weather stations
- Drone / quadcopter flight controller peripherals
- Wearable motion and environment tracking
- Robot orientation sensing
- Industrial condition monitoring

---

## Project Status

| Stage            | Status       |
|------------------|--------------|
| Schematic        | ✅ Complete  |
| PCB Layout       | ✅ Complete  |
| DRC              | ✅ Passed    |
| Gerbers Exported | ✅ Ready     |
| Fabricated       | ⬜ Not yet   |
| Tested           | ⬜ Not yet   |

---

## About the Designer

Self-taught PCB designer specializing in KiCad — IoT, embedded systems, and industrial control boards.
Available for freelance PCB design work: schematic capture, layout, DRC review, and Gerber preparation.

🔗 GitHub: [Abhi90808]
📧 [kvabhishek908@gmail.com]

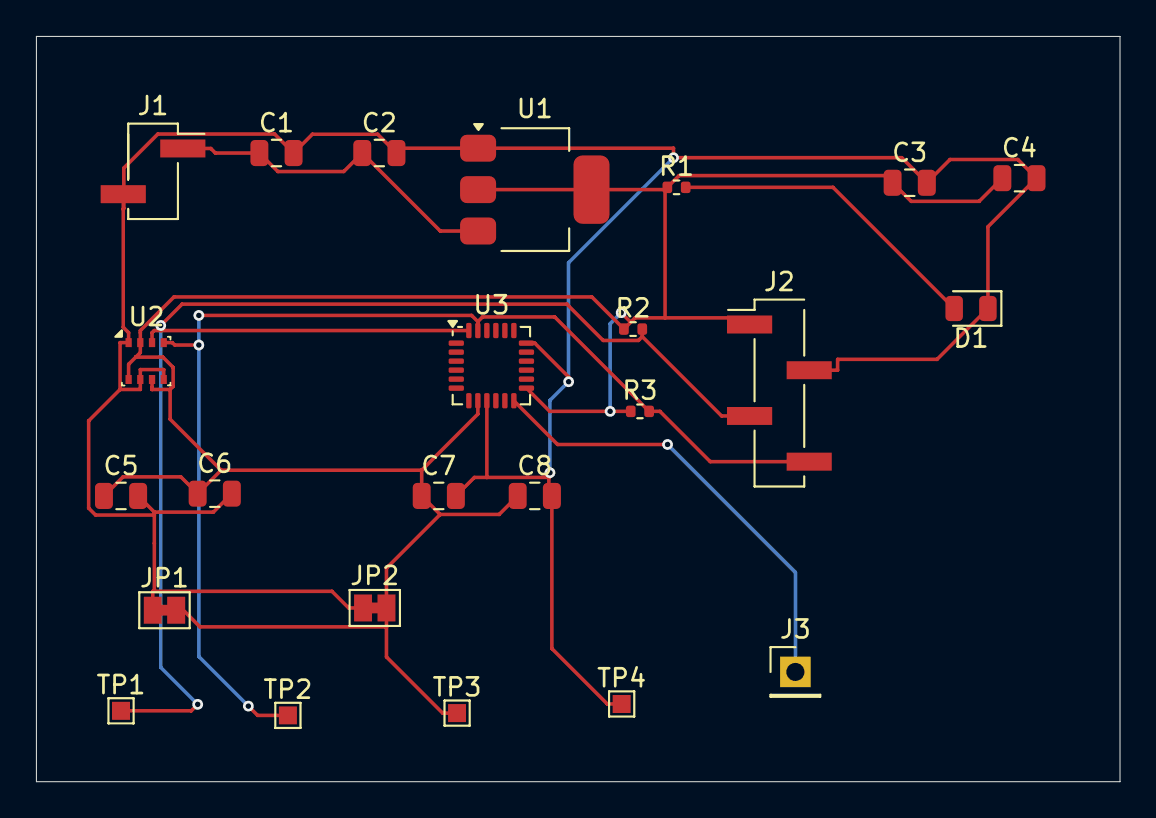
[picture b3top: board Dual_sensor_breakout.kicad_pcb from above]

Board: 2 copper layers, 60.2 x 41.4 mm, 24 parts (0 on the bottom side), 7 nets.

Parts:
C1, C3: 10uf; C_0805_2012Metric
C2, C4, C5, C6, C7, C8: 100nf; C_0805_2012Metric
D1: LED_Green; LED_0805_2012Metric
J1: PWR_IN; PinHeader_1x02_P2.54mm_Vertical_SMD_Pin1Right
J2: I2C_HEADER; PinHeader_1x04_P2.54mm_Vertical_SMD_Pin1Left
J3: INT_OUT; PinHeader_1x01_P2.54mm_Vertical
JP1: BME280_ADDR; SolderJumper-2_P1.3mm_Bridged_Pad1.0x1.5mm
JP2: MPU6050_ADDR; SolderJumper-2_P1.3mm_Bridged_Pad1.0x1.5mm
R1: 1k; R_0402_1005Metric
R2, R3: 4.7k; R_0402_1005Metric
TP1: TP_SDA; TestPoint_Pad_1.0x1.0mm
TP2: TP_SCL; TestPoint_Pad_1.0x1.0mm
TP3: TP_3V3; TestPoint_Pad_1.0x1.0mm
TP4: TP_GND; TestPoint_Pad_1.0x1.0mm
U1: AMS1117-3.3; SOT-223-3_TabPin2
U2: BME280; Bosch_LGA-8_2.5x2.5mm_P0.65mm_ClockwisePinNumbering
U3: MPU-6050; InvenSense_QFN-24_4x4mm_P0.5mm

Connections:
+3.3V: C3.1, C4.1, C5.1, C6.1, C7.1, C8.1, J2.1, JP1.2 (B), JP2.2 (B), R1.1, R2.1, R3.1, TP3.1, U1.2 (VO), U2.2 (CSB), U2.6 (VDDIO), U2.8 (VDD), U3.8 (VLOGIC), U3.13 (VDD)
+5V: C1.1, C2.1, J1.1, U1.3 (VI)
/INT: J3.1, U3.12 (INT)
/SCL: J2.4, R3.2, TP2.1, U2.4 (SCK), U3.23 (SCL)
/SDA: J2.3, R2.2, TP1.1, U2.3 (SDI), U3.24 (SDA)
GND: C1.2, C2.2, C3.2, C4.2, C5.2, C6.2, C7.2, C8.2, D1.1 (K), J1.2, J2.2, JP1.1 (A), JP2.1 (A), TP4.1, U1.1 (GND), U2.1 (GND), U2.5 (SDO), U2.7 (GND), U3.9 (AD0), U3.18 (GND)
unnamed: D1.2 (A), R1.2

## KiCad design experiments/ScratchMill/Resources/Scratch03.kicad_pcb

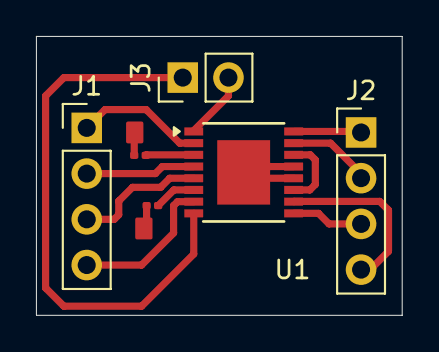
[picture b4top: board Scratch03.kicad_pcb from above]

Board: 2 copper layers, 20.3 x 15.5 mm, 6 parts (0 on the bottom side), 14 nets.

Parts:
J1: MotorOut; PinHeader_1x04_P2.54mm_Vertical
J2: Motor_In; PinHeader_1x04_P2.54mm_Vertical
J3: State; PinHeader_1x02_P2.54mm_Vertical
R1, R2: R; R_0201_0603Metric
U1: DRV8848; TSSOP-16-1EP_4.4x5mm_P0.65mm

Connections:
GND: R1.1, R2.1, U1.12 (VM), U1.13 (GND), U1.17 (GND)
MA1: J1.1, U1.2 (AOUT1)
MA2: J1.2, U1.4 (AOUT2)
MB1: J1.4, U1.7 (BOUT1)
MB2: J1.3, U1.5 (BOUT2)
unnamed: J2.1, U1.16 (AIN1)
unnamed: J2.2, U1.15 (AIN2)
unnamed: J2.3, U1.9 (BIN1)
unnamed: J2.4, U1.10 (BIN2)
unnamed: J3.1, U1.8 (~FAULT)
unnamed: J3.2, U1.1 (~SLEEP)
unnamed: R1.2, U1.3 (AISEN)
unnamed: R2.2, U1.6 (BISEN)
unnamed: U1.11 (VREF), U1.14 (VINT)
